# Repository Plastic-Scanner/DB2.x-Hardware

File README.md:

# DB2.x-Hardware

>CAUTION  
This is still an early development prototype. We recommend all makers, hackers and contributors to wait until the next development board release, where we will focus on making it reproducible and invite everyone to collaborate on.  

Hi and welcome to the hardware package of the Development Board 2.x
this repository is meant to host files and have releases. 

Learn more about the development board by visiting our [documentation page](https://docs.plasticscanner.com/boards/DB2.2).  
<!-- Find the firmware for the development board [here](https://github.com/Plastic-Scanner/DB2.x-Firmware) -->

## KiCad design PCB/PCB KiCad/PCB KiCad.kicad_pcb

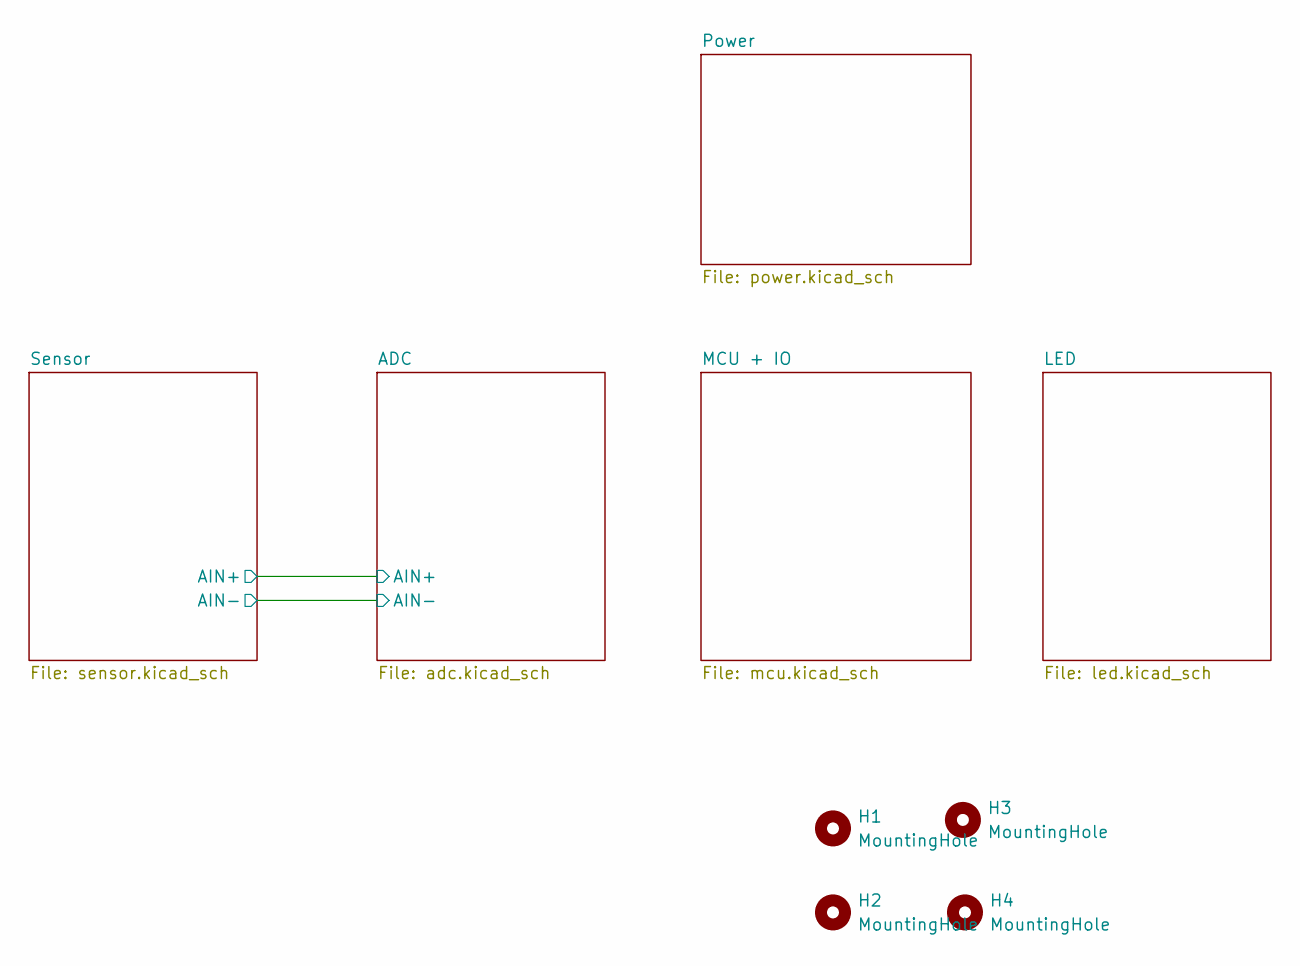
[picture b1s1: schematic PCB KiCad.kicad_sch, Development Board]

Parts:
H1, H2, H3, H4: MountingHole; MountingHole_3.2mm_M3

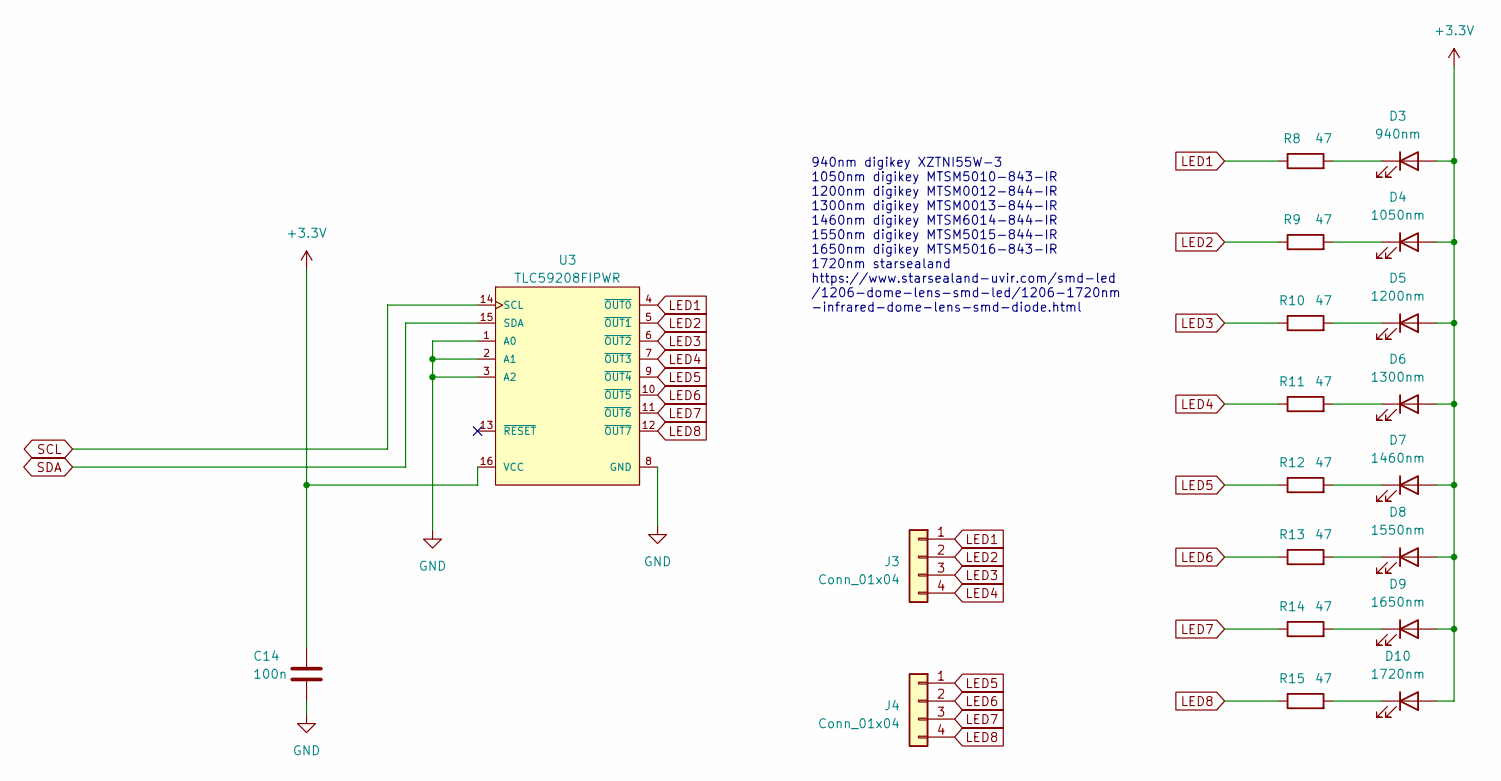
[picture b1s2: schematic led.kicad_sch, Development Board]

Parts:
C14: 100n; C_0805_2012Metric_Pad1.18x1.45mm_HandSolder
D3: 940nm; LED_1206_3216Metric_Pad1.42x1.75mm_HandSolder
D4: 1050nm; LED_1206_3216Metric_Pad1.42x1.75mm_HandSolder
D5: 1200nm; LED_1206_3216Metric_Pad1.42x1.75mm_HandSolder
D6: 1300nm; LED_1206_3216Metric_Pad1.42x1.75mm_HandSolder
D7: 1460nm; LED_1206_3216Metric_Pad1.42x1.75mm_HandSolder
D8: 1550nm; LED_1206_3216Metric_Pad1.42x1.75mm_HandSolder
D9: 1650nm; LED_1206_3216Metric_Pad1.42x1.75mm_HandSolder
D10: 1720nm; LED_1206_3216Metric_Pad1.42x1.75mm_HandSolder
J3, J4: Conn_01x04; PinSocket_1x04_P2.54mm_Vertical
R8, R9, R10, R11, R12, R13, R14, R15: 47; R_0805_2012Metric_Pad1.20x1.40mm_HandSolder
U3: TLC59208FIPWR; Texas_Instruments-TLC59208FIPWR-Level_A

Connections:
3.3v: C14.1, D3.2 (A), D4.2 (A), D5.2 (A), D6.2 (A), D7.2 (A), D8.2 (A), D9.2 (A), D10.2 (A), U3.16 (VCC); also elsewhere on the board
GND: C14.2, U3.1 (A0), U3.2 (A1), U3.3 (A2), U3.8 (GND); also elsewhere on the board
LED1: J3.1, R8.1, U3.4 (~OUT0)
LED2: J3.2, R9.1, U3.5 (~OUT1)
LED3: J3.3, R10.1, U3.6 (~OUT2)
LED4: J3.4, R11.1, U3.7 (~OUT3)
LED5: J4.1, R12.1, U3.9 (~OUT4); also elsewhere on the board
LED6: J4.2, R13.1, U3.10 (~OUT5); also elsewhere on the board
LED7: J4.3, R14.1, U3.11 (~OUT6); also elsewhere on the board
LED8: J4.4, R15.1, U3.12 (~OUT7); also elsewhere on the board
unnamed: D3.1 (K), R8.2
unnamed: D4.1 (K), R9.2
unnamed: D5.1 (K), R10.2
unnamed: D6.1 (K), R11.2
unnamed: D7.1 (K), R12.2
unnamed: D8.1 (K), R13.2
unnamed: D9.1 (K), R14.2
unnamed: D10.1 (K), R15.2
SCL: U3.14 (SCL); also elsewhere on the board
SDA: U3.15 (SDA); also elsewhere on the board

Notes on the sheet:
940nm digikey XZTNI55W-3 1050nm digikey MTSM5010-843-IR 1200nm digikey MTSM0012-844-IR 1300nm digikey MTSM0013-844-IR 1460nm digikey MTSM6014-844-IR 1550nm digikey MTSM5015-844-IR 1650nm digikey MTSM5016-843-IR 1720nm starsealand https://www.starsealand-uvir.com/smd-led /1206-dome-lens-smd-led/1206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

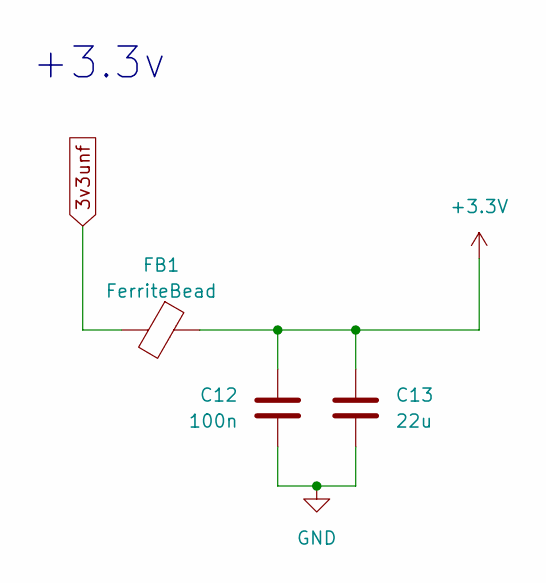
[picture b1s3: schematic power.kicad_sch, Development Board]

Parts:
C12: 100n; C_0805_2012Metric_Pad1.18x1.45mm_HandSolder
C13: 22u; C_0805_2012Metric_Pad1.18x1.45mm_HandSolder
FB1: FerriteBead; R_0805_2012Metric_Pad1.20x1.40mm_HandSolder

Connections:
3.3v: C12.2, C13.1, FB1.1; also elsewhere on the board
3v3unf: FB1.2; also elsewhere on the board
GND: C12.1, C13.2; also elsewhere on the board

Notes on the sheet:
+3.3v

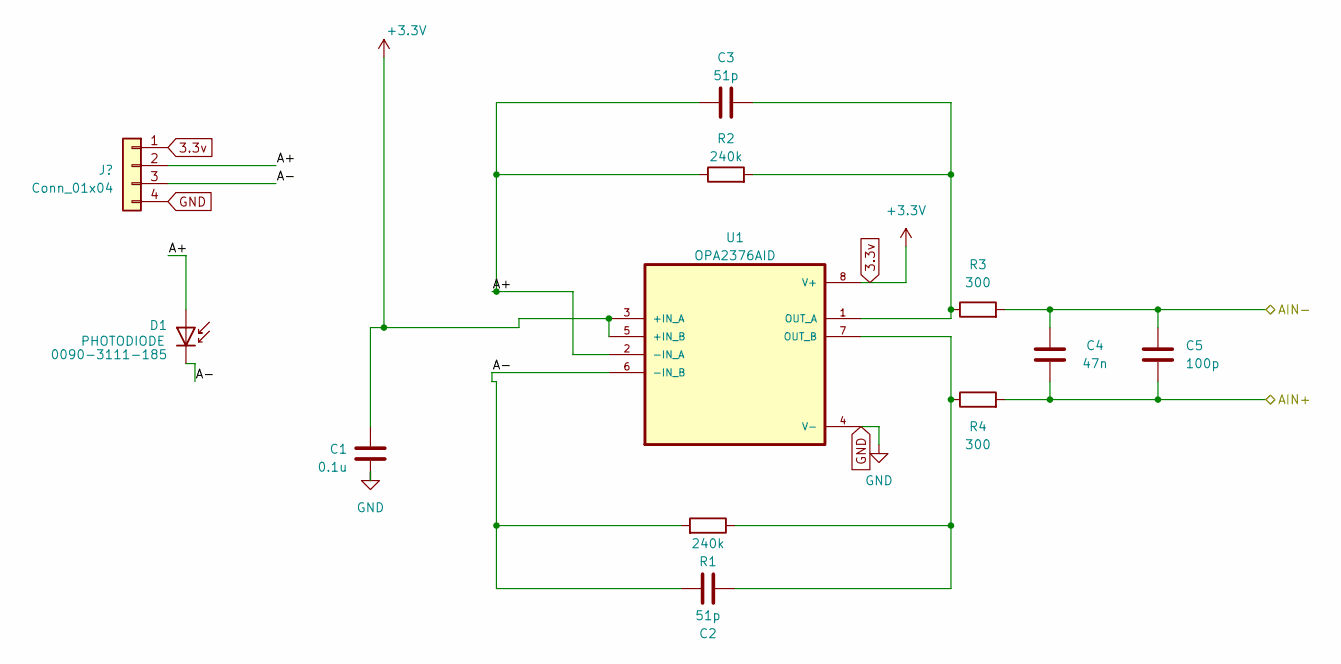
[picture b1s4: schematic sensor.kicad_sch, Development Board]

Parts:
C1: 0.1u; C_0805_2012Metric_Pad1.18x1.45mm_HandSolder
C2, C3: 51p; C_0805_2012Metric_Pad1.18x1.45mm_HandSolder
C4: 47n; C_0805_2012Metric_Pad1.18x1.45mm_HandSolder
C5: 100p; C_0805_2012Metric_Pad1.18x1.45mm_HandSolder
D1: 0090-3111-185; D_A-405_P2.54mm_Vertical_KathodeUp
J1: Conn_01x04; PinSocket_1x04_P2.54mm_Vertical
R1, R2: 240k; R_0805_2012Metric_Pad1.20x1.40mm_HandSolder
R3, R4: 300; R_0805_2012Metric_Pad1.20x1.40mm_HandSolder
U1: OPA2376AID; SOIC127P599X175-8N

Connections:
3.3v: C1.2, J1.1, U1.3 (+IN_A), U1.5 (+IN_B), U1.8 (V+); also elsewhere on the board
/ADC/AIN+: C4.1, C5.2, R4.2; also elsewhere on the board
/ADC/AIN-: C4.2, C5.1, R3.2; also elsewhere on the board
/Sensor/A+: C3.1, D1.2 (A), J1.2, R2.1, U1.2 (-IN_A)
/Sensor/A-: C2.1, D1.1 (K), J1.3, R1.2, U1.6 (-IN_B)
GND: C1.1, J1.4, U1.4 (V-); also elsewhere on the board
unnamed: C3.2, R2.2, R3.1, U1.1 (OUT_A)
unnamed: C2.2, R1.1, R4.1, U1.7 (OUT_B)

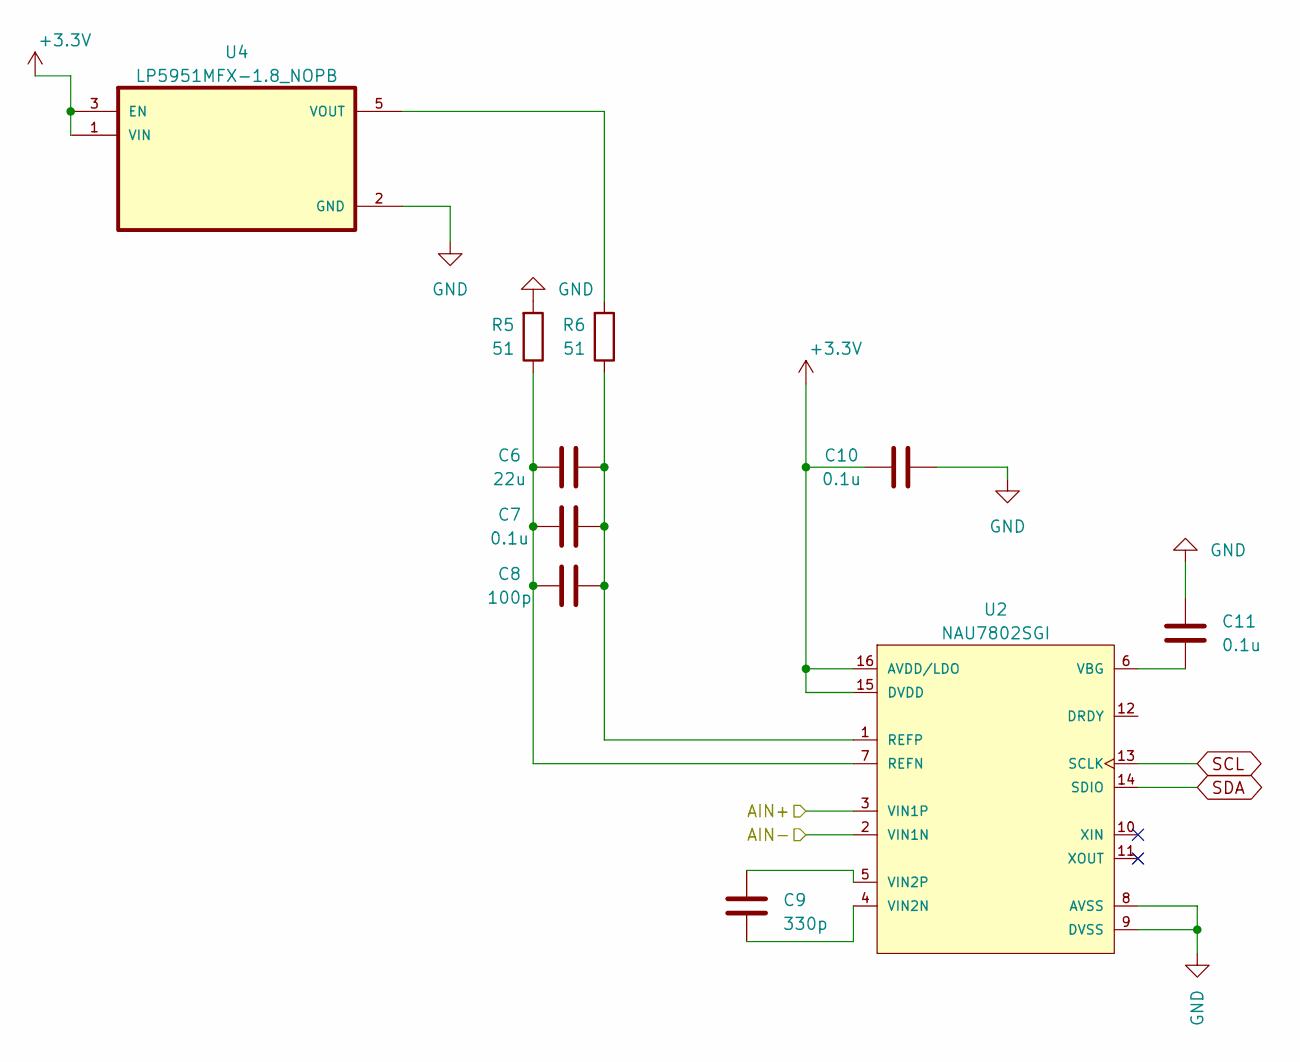
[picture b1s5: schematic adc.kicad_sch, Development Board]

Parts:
C6: 22u; C_0805_2012Metric_Pad1.18x1.45mm_HandSolder
C7, C10, C11: 0.1u; C_0805_2012Metric_Pad1.18x1.45mm_HandSolder
C8: 100p; C_0805_2012Metric_Pad1.18x1.45mm_HandSolder
C9: 330p; C_0805_2012Metric_Pad1.18x1.45mm_HandSolder
R5, R6: 51; R_0805_2012Metric_Pad1.20x1.40mm_HandSolder
U2: NAU7802SGI; Nuvoton-NAU7802SGI-0-0-0; digikey description IC ADC 24BIT I2C/SRL 16-SOP
U4: LP5951MFX-1.8_NOPB; SOT95P280X145-5N

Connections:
3.3v: C10.1, U2.15 (DVDD), U2.16 (AVDD/LDO), U4.1 (VIN), U4.3 (EN); also elsewhere on the board
/ADC/AIN+: U2.3 (VIN1P); also elsewhere on the board
/ADC/AIN-: U2.2 (VIN1N); also elsewhere on the board
GND: C10.2, C11.1, R5.2, U2.8 (AVSS), U2.9 (DVSS), U4.2 (GND); also elsewhere on the board
unnamed: C6.1, C7.1, C8.1, R5.1, U2.7 (REFN)
unnamed: C6.2, C7.2, C8.2, R6.1, U2.1 (REFP)
unnamed: C11.2, U2.6 (VBG)
unnamed: C9.2, U2.4 (VIN2N)
unnamed: C9.1, U2.5 (VIN2P)
unnamed: R6.2, U4.5 (VOUT)
SCL: U2.13 (SCLK); also elsewhere on the board
SDA: U2.14 (SDIO); also elsewhere on the board

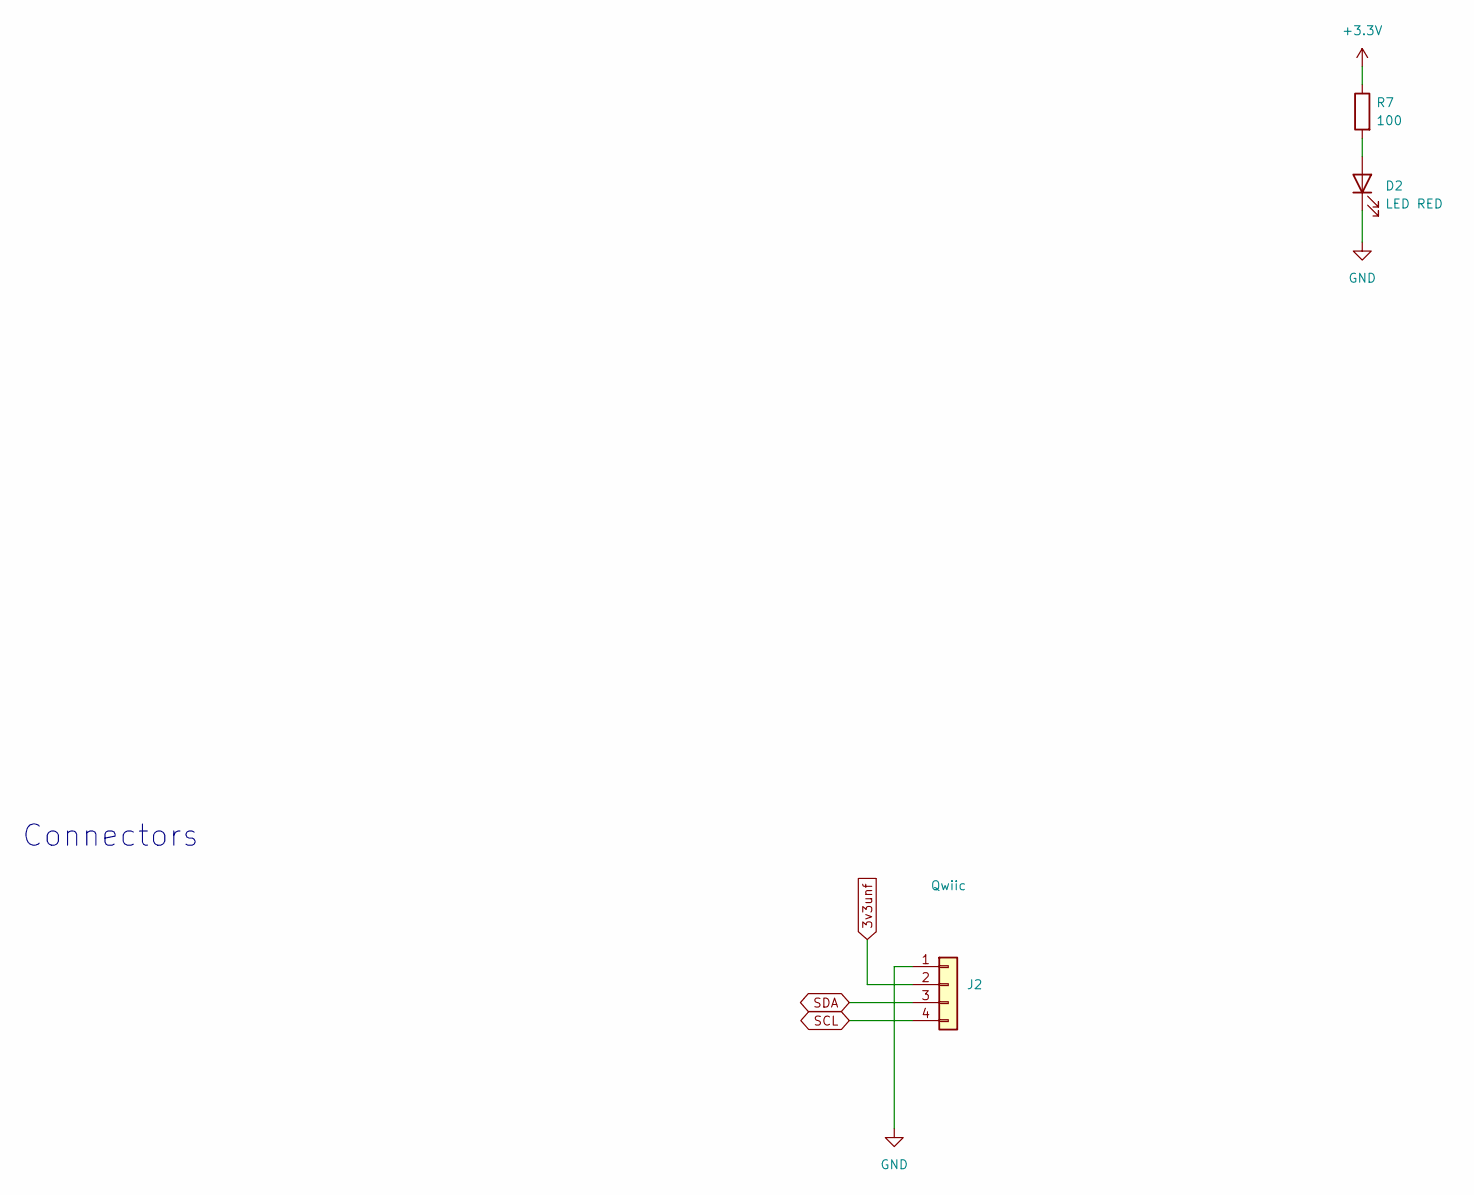
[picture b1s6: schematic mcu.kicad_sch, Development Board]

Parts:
D2: LED RED; LED_0805_2012Metric_Pad1.15x1.40mm_HandSolder
J2: Qwiic; JST_SH_SM04B-SRSS-TB_1x04-1MP_P1.00mm_Horizontal
R7: 100; R_0805_2012Metric_Pad1.20x1.40mm_HandSolder

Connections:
3.3v: R7.1; also elsewhere on the board
3v3unf: J2.2; also elsewhere on the board
GND: D2.1 (K), J2.1; also elsewhere on the board
unnamed: D2.2 (A), R7.2
SCL: J2.4; also elsewhere on the board
SDA: J2.3; also elsewhere on the board

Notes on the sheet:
Connectors

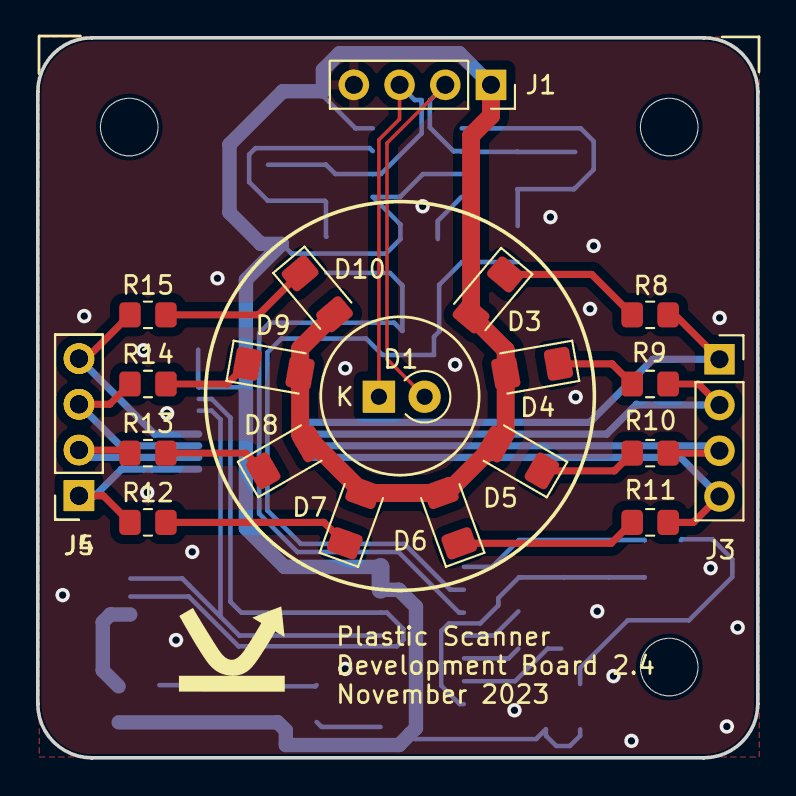
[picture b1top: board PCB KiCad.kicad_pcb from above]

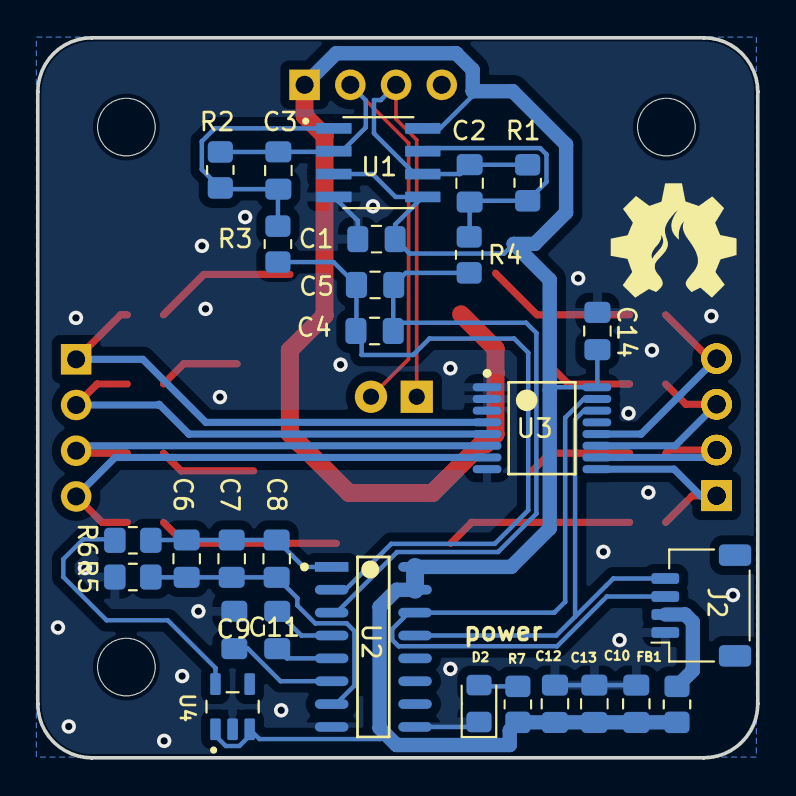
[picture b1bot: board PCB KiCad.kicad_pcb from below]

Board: 2 copper layers, 40.0 x 40.0 mm, 52 parts (28 on the bottom side), 34 nets.

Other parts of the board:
J5: Conn_01x04; PinSocket_1x04_P2.54mm_Vertical

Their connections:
LED5: J5.1; also elsewhere on the board
LED6: J5.2; also elsewhere on the board
LED7: J5.3; also elsewhere on the board
LED8: J5.4; also elsewhere on the board

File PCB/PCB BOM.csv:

"Id";"Designator";"Footprint";"Quantity";"Designation";"Supplier and ref";
1;"D5";"LED_1206_3216Metric_Pad1.42x1.75mm_HandSolder";1;"1050nm";;;
2;"mouse-bite-2mm-slot,mouse-bite-2mm-slot,mouse-bite-2mm-slot,mouse-bite-2mm-slot,mouse-bite-2mm-slot,mouse-bite-2mm-slot";"mouse-bite-2mm-slot";6;"VAL**";;;
3;"D12,D3";"LED_0805_2012Metric_Pad1.15x1.40mm_HandSolder";2;"LED RED";;;
4;"R15,R17,R21,R16,R19,R20,R22,R18";"R_0805_2012Metric_Pad1.20x1.40mm_HandSolder";8;"47";;;
5;"D1";"D_1206_3216Metric_Pad1.42x1.75mm_HandSolder";1;"0090-3111-185";;;
6;"R6,R5";"R_0805_2012Metric_Pad1.20x1.40mm_HandSolder";2;"51";;;
7;"R9,R10";"R_0805_2012Metric_Pad1.20x1.40mm_HandSolder";2;"10k";;;
8;"J3";"JST_SH_SM04B-SRSS-TB_1x04-1MP_P1.00mm_Horizontal";1;"Qwiic";;;
9;"C5,C8";"C_0805_2012Metric_Pad1.18x1.45mm_HandSolder";2;"100p";;;
10;"D10";"LED_1206_3216Metric_Pad1.42x1.75mm_HandSolder";1;"1650nm";;;
11;"U1";"SOIC127P599X175-8N";1;"OPA2376AID";;;
12;"C13";"C_0805_2012Metric_Pad1.18x1.45mm_HandSolder";1;"10u";;;
13;"C10,C7,C1,C11";"C_0805_2012Metric_Pad1.18x1.45mm_HandSolder";4;"0.1u";;;
14;"D9";"LED_1206_3216Metric_Pad1.42x1.75mm_HandSolder";1;"1550nm";;;
15;"U2";"Nuvoton-NAU7802SGI-0-0-0";1;"NAU7802SGI";;;
16;"C4";"C_0805_2012Metric_Pad1.18x1.45mm_HandSolder";1;"47n";;;
17;"A1";"Arduino_UNO_R3";1;"Arduino_UNO_R3";;;
18;"C16,C14";"C_0805_2012Metric_Pad1.18x1.45mm_HandSolder";2;"100n";;;
19;"C6,C15";"C_0805_2012Metric_Pad1.18x1.45mm_HandSolder";2;"22u";;;
20;"R4,R3";"R_0805_2012Metric_Pad1.20x1.40mm_HandSolder";2;"300";;;
21;"R2,R1";"R_0805_2012Metric_Pad1.20x1.40mm_HandSolder";2;"240k";;;
22;"FB1";"R_0805_2012Metric_Pad1.20x1.40mm_HandSolder";1;"FerriteBead";;;
23;"C9";"C_0805_2012Metric_Pad1.18x1.45mm_HandSolder";1;"330p";;;
24;"D6";"LED_1206_3216Metric_Pad1.42x1.75mm_HandSolder";1;"1200nm";;;
25;"J5,J1,J4";"PinSocket_1x04_P2.54mm_Vertical";3;"Conn_01x04";;;
26;"SW2";"SW_PUSH_6mm";1;"TRIGGER";;;
27;"D7";"LED_1206_3216Metric_Pad1.42x1.75mm_HandSolder";1;"1300nm";;;
28;"U4";"Texas_Instruments-TLC59208FIPWR-Level_A";1;"TLC59208FIPWR";;;
29;"D4";"LED_1206_3216Metric_Pad1.42x1.75mm_HandSolder";1;"940nm";;;
30;"R7,R11,R8";"R_0805_2012Metric_Pad1.20x1.40mm_HandSolder";3;"100";;;
31;"J2";"PinHeader_1x08_P2.54mm_Vertical";1;"Conn_01x08";;;
32;"D11";"LED_1206_3216Metric_Pad1.42x1.75mm_HandSolder";1;"1720nm";;;
33;"R14";"R_0805_2012Metric_Pad1.20x1.40mm_HandSolder";1;"1k";;;
34;"U3";"SOT-223-3_TabPin2";1;"AMS1117-3.3";;;
35;"D8";"LED_1206_3216Metric_Pad1.42x1.75mm_HandSolder";1;"1460nm";;;
36;"C2,C3";"C_0805_2012Metric_Pad1.18x1.45mm_HandSolder";2;"51p";;;
37;"D2";"LED_0805_2012Metric_Pad1.15x1.40mm_HandSolder";1;"LED BLUE";;;
38;"SW1";"SW_PUSH_6mm";1;"MCU_RESET";;;

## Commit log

2022-02-17 Initial collection of information
2022-02-23 Added easyeda project, made a better pinout
2022-02-23 Fix of links to external websites
2022-03-01 ready for public
2022-03-07 Basic KiCad structure with gitignore file
2022-03-07 draw schematic for 60%
2022-03-09 Add buttons: MCU RESET, TRIGGER
2022-03-09 Ignore autosaved files, cleanup MCU schematics
2022-03-09 first check + add connectors
2022-03-09 ERC: add power flags to satisfy the ERC crap
2022-03-09 Satisfy the overdemanding attention hungry ERC monster
2022-03-09 Add footprints
2022-03-09 Add board outline
2022-03-09 start of component placement
2022-03-09 Added missing footprint symbols
2022-03-09 placement of components
2022-03-10 placement: working on the analog frontend
2022-03-10 placement: rough layout done
2022-03-10 routing: high-speed and sensitive signal routing done
2022-03-10 routing: power pins connected
2022-03-10 routing: fix J2 orientation (more intuitive)
2022-03-11 routing: swap order of J1 ADC signals, swap buttons order
2022-03-11 routing: add ground plane, finish all tracks
2022-03-14 silkscreen and thicker traces
2022-03-15 Fixed mounting holes, added logo
2022-03-15 export for review
2022-03-16 update CAD files
2022-03-16 update media files
2022-03-16 PCB at time of order
2022-03-16 Delete PCB/PCB KiCad/PCB KiCad-backups directory
    show have been in gitignore
2022-03-16 fix image in README
2022-04-04 fixes issue #09 and adds gnd testpad to make testing easier
2022-04-04 adds gerber.zip file, because gitignore file was wrong
2022-04-11 Adds 1720nm datasheet and corrects some typ's
2022-05-10 adds PCB Pinout
2022-05-18 adds wavelengths to BOM
2022-06-10 fix broken link in readme
2022-06-21 adds pinout image
2023-02-24 new datasheet 1720nm led
2023-02-27 adds correct values of current limiting resistors for LEDs
2023-02-27 adds hardwarce and documentation license
2023-04-22 v2.2.0 first attempt for new ICs
2023-05-09 updated CAD
2023-05-09 updated media
2023-05-09 update pcb
2023-05-09 update reference files
2023-05-09 add pcb pinout pdf
2023-09-12 typo
2023-09-12 Fix picture
2023-10-24 idea for small round pcb
2023-11-06 pre route
2023-11-06 routed!
2023-11-06 adds LP5951MFX
2023-11-09 square pcb
2024-01-30 add 3D files
2024-01-30 add correct license
